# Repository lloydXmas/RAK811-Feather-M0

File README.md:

# RAK811 FeatherWing for the Feather M0  

This shield gives LoRaWAN connectivity to Adafruit's Feather M0 via the RAK811 module. Examples directory demonstrate usage/configuration with The Things Network.

Advantages of using the RAK811:
* Compared to other full-stack devices, the RAK811 is small in size and fits nicely on FeatherWing dimensions.
* Using an LMIC library to run a full LoRaWAN stack on the M0 can be challenging when interrupts and delays are needed.
* By removing the LoRaWAN stack from the M0, more flash memory is available.

The M0 has 6 possible serial communication (SERCOM) interfaces. The shield has a DPDT switch to select which SERCOM is used for RAK811 communication:
* `Serial1` uses the default UART RX/TX pins at D0 and D1. 
* `Serial2` uses pins D10 and D11 for RX/TX (Examples assume Serial2 is used)

## Updating the RAK811 Module
The board has a UART breakout for updating the RAK811's firmware and bootloader as newer versions are released.
To update the bootloader with the STM32CubeProgrammer, add solder to the jumper on the bottom of PCB. Remove solder to update firmware.

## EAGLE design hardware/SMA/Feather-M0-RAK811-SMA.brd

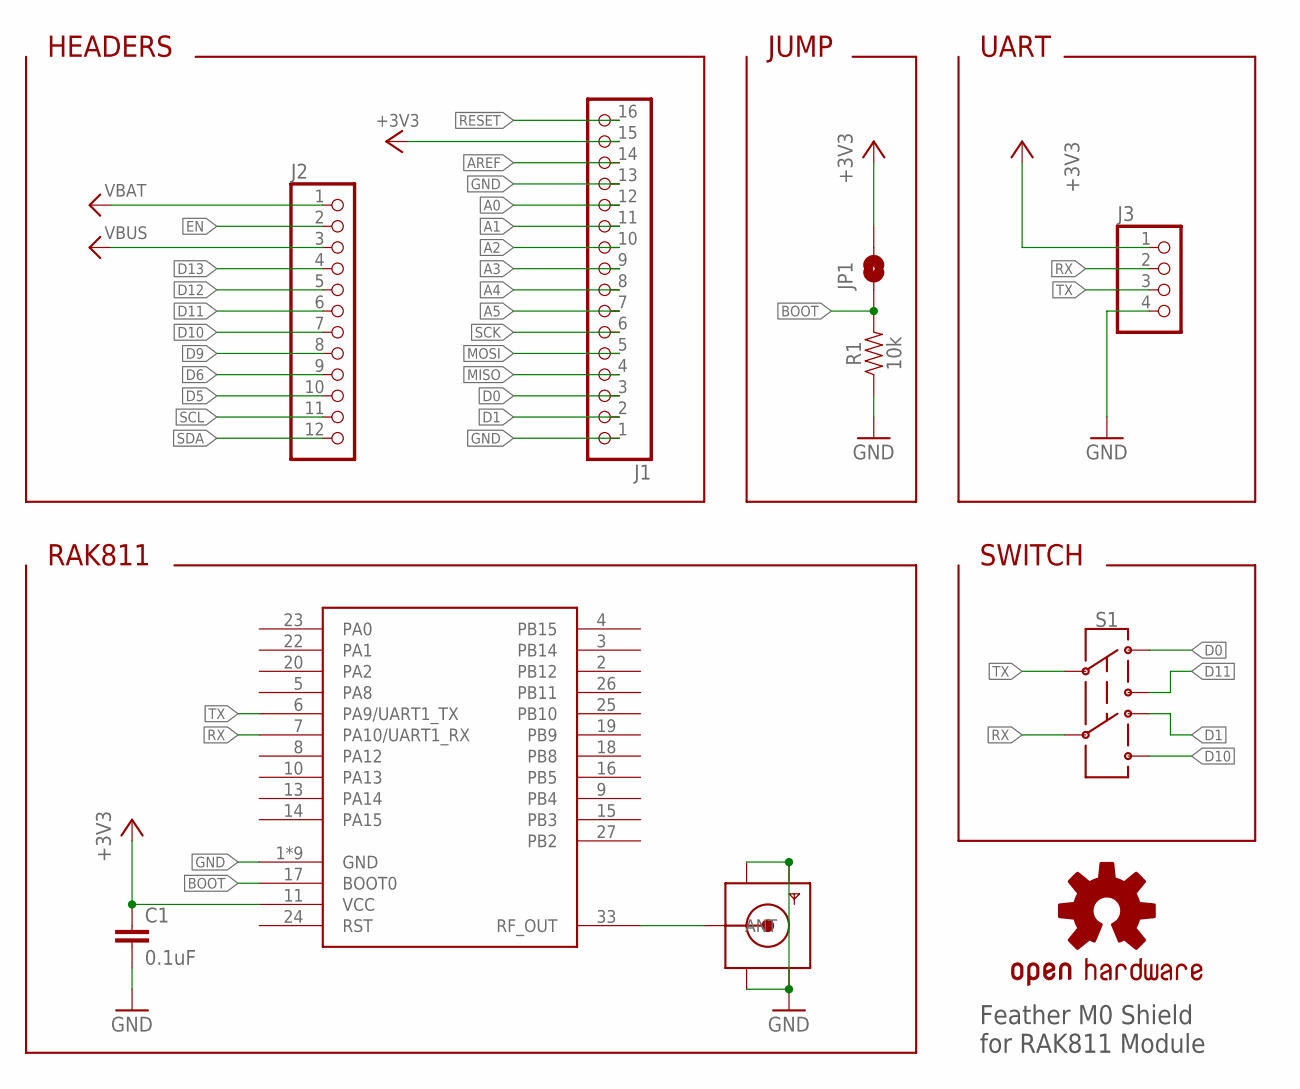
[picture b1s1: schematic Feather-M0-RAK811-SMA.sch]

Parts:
C1: 0.1uF; 0603
J1: HEADER-1X16ROUND; 1X16_ROUND
J2: HEADER-1X12; 1X12_ROUND
J3: HEADER-1X4ROUND; 1X04_ROUND
JP1: JUMPER-SMT_2_NO_SILK; SMT-JUMPER_2_NO_SILK
LOGO1: OSHW-LOGOS; OSHW-LOGO-S
R1: 10k; 0603
S1: SWITCH-DPDT-SMD-AYZ0202; SWITCH_DPDT_SMD_AYZ0202
U1: RAK_WIRELESS_RAK811
X1: SMACONNECTOR_EDGE; SMA_EDGELAUNCH

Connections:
!RESET: J1.16
+3V3: C1.1, J1.15, J3.1, JP1.2, U1.11 (VCC)
A0: J1.12
A1: J1.11
A2: J1.10
A3: J1.9
A4: J1.8
A5: J1.7
AREF: J1.14
BOOT: JP1.1, R1.2, U1.17 (BOOT0)
D0: J1.3, S1.1
D1: J1.2, S1.4
D5: J2.10
D6: J2.9
D9: J2.8
D10: J2.7, S1.6
D11: J2.6, S1.3
D12: J2.5
D13: J2.4
EN: J2.2
GND: C1.2, J1.1, J1.13, J3.4, R1.1, U1.1 (GND), U1.12 (GND), U1.21 (GND), U1.28 (GND), U1.29 (GND), U1.30 (GND), U1.31 (GND), U1.32 (GND), U1.34 (GND), X1.GND@1 (GND4), X1.GND@2 (GND3), X1.GND@3 (GND2), X1.GND@4 (GND1)
MISO: J1.4
MOSI: J1.5
RF: U1.33 (RF_OUT), X1.P (ANT)
RX: J3.2, S1.5, U1.7 (PA10/UART1_RX)
SCK: J1.6
SCL: J2.11
SDA: J2.12
TX: J3.3, S1.2, U1.6 (PA9/UART1_TX)
VBAT: J2.1
VBUS: J2.3

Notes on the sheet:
UART
HEADERS
JUMP
RAK811
Feather M0 Shield for RAK811 Module
SWITCH

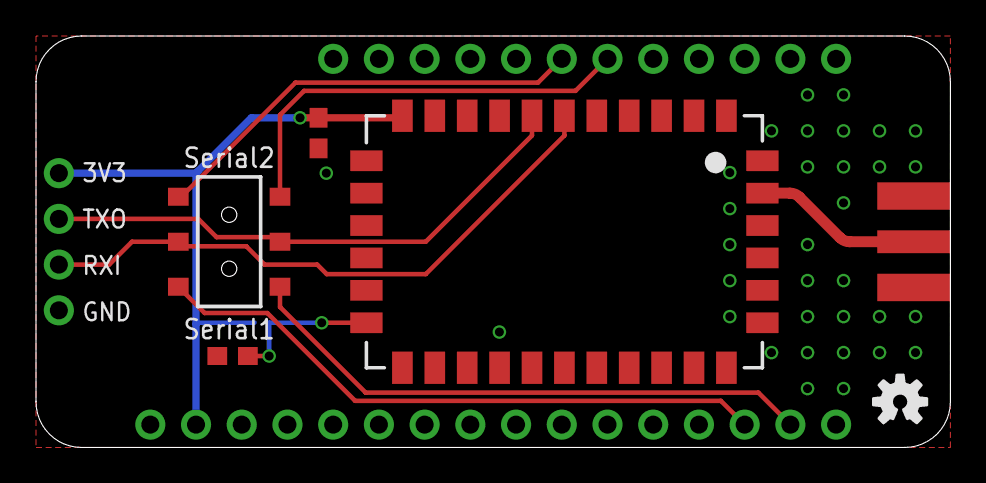
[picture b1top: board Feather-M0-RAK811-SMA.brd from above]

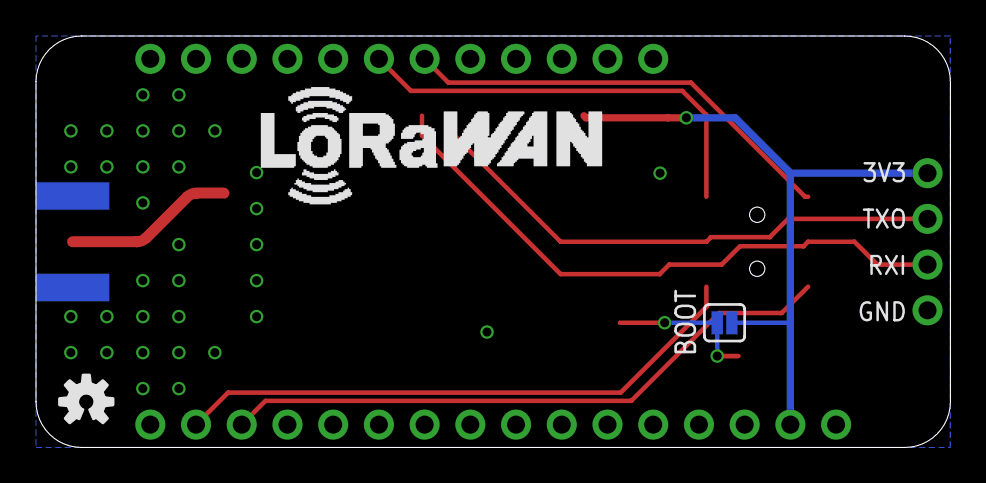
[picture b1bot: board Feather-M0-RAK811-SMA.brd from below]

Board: 2 copper layers, 50.8 x 22.9 mm, 12 parts (3 on the bottom side), 10 nets.

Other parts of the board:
LOGO2: OSHW-LOGOS; OSHW-LOGO-S
U$1: LORAWAN

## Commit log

2019-12-17 inital commit
2019-12-17 README fix
2020-02-13 rendering

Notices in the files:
parts and their libraries:
microbuilder: This work is placed in the public domain, and may be freely used for commercial and non-commercial work with the following conditions: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
SparkFun-Jumpers: Licensing: Creative Commons ShareAlike 4.0 International - https://creativecommons.org/licenses/by-sa/4.0
